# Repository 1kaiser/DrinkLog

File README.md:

# 💧 DrinkLog — Concept Universal Waterproof BLE Smart Bottle-Cap Hydration Tracker

<p align="center">

</p>

> [!NOTE]
> **Concept & Reference Design:** DrinkLog is currently a **pre-prototype hardware and software concept**. No physical PCB, enclosure, strain-gauge flexure, or live BLE/USB-C unit has been fabricated or bench-tested yet. All power budgets, mechanical tolerances, PCBWay deliverables, firmware modules, and companion code are validated in software/simulation only (`C++17` unit tests, `pytest`, programmatic DRC/STL/DXF checks, and Dawn WebGPU/WASM + Three.js renders). Review KiCad footprints, RF antenna clearance, IP67 seal compression, and mechanical fits before ordering prototype hardware.

**DrinkLog** is a conceptual, ultra-thin (`11.0 mm` added cap height), rechargeable, **IP67 waterproof USB-C** smart bottle-cap gripper proportioned at **`1.10 × D_cap`** (`33.6 mm` for standard PET water bottles up to `69.3 mm` for wide-mouth flasks) around a **universal `Ø 28.0 mm` drop-in PCBWay core** designed to measure fluid consumed from **pick-up / put-down gravimetric weight differences** and log every sip into **Android Health Connect** (`HydrationRecord`).

Everything needed to review, simulate, and prototype the concept — **3D-printable STLs**, **laser-cut flexure DXF**, **PCBWay Gerber/BOM/CPL & KiCad 8 files**, **firmware**, **Node.js + Clang `wasm32` + Native Dawn WebGPU animation (`webgpu-dawn-wasm/`)**, **interactive Three.js viewer (`web-threejs/`)**, and **BLE/Health Connect companion code** — lives in this repository.

---

## ✨ Key Highlights

* 📐 **`1.10 × D_cap` Zero-Overhang Proportions:** Instead of a bulky universal puck overhanging a small PET bottle, DrinkLog scales cleanly across 4 standard cap tiers (`33.6 / 45.1 / 52.8 / 69.3 mm`) while sharing **one universal `Ø 28.0 mm` PCBWay PCBA + `Ø 30.0 mm` 301-SS flexure core** across all 4 shells:
  | Tier Preset | Bottle Type | Nominal Cap OD (`D_cap`) | DrinkLog OD (`1.10 × D_cap`) | Battery |
  | :--- | :--- | :---: | :---: | :---: |
  | **`pet_30`** *(Default)* | Standard PET Water / Soda (`28 mm` neck) | `30.5 mm` | **`33.6 mm`** | `401520` (`100 mAh`, ~`8.0 mo`) |
  | **`sport_40`** | Sports / Wide PET (`38 mm` neck) | `41.0 mm` | **`45.1 mm`** | `302030` (`150 mAh`, ~`11.8 mo`) |
  | **`flask_48`** | Insulated Standard Flask | `48.0 mm` | **`52.8 mm`** | `302030` (`150 mAh`, ~`11.8 mo`) |
  | **`wide_63`** | Wide-Mouth Hydro Flask / Nalgene | `63.0 mm` | **`69.3 mm`** | `302030` (`150 mAh`, ~`11.8 mo`) |
* ⚖️ **Moment-Cancelling 3-Spoke Flexure:** Universal **`Ø 30.0 mm × 0.8 mm`** laser-cut `301-SS` flexure with `4× BF1000-2AA` (`1000 Ω`) full Wheatstone bridge and `0.35 mm` drop hard-stops rejects off-axis tilt moments and twisting torque.
* 🔋 **8–12 Months per Charge (`6.4 µA` Standby):** `NAU7802YG` (`QFN-16`) switches its internal `2.4 V AVDD` LDO to **High-Z** between lifts (`0 µA` bridge leak), paired with a `0.9 µA` **Bosch BMA400** wake-on-lift IMU.
* 🔌 **Waterproof USB-C Charging + Dual Debug:** Uses an **Amphenol `12402448E512A` IPX8 mid-mount USB-C** port + captive `TPU 85A` plug + **Raytac `MDBT50Q-1MV2` (`nRF52840`)** for native USB 2.0 CDC serial calibration (`s`, `t`, `c <g>`, `d`, `b` UF2/DFU) AND a zero-height bottom **Tag-Connect `TC2030` SWD** footprint.
* 🏭 **Turnkey PCBWay Ready:** Full KiCad 8 project (`Ø 28.0 mm`, `0.8 mm` 4L ENIG), RS-274X Gerbers + Excellon drills, matching 1:1 BOM & Centroid CPL CSVs, `Ø 30.0 mm` sheet-metal DXF, and 8 split 3D-printable STLs.

---

## 🧩 Hardware Components & Architecture

<details>
<summary><b>🔬 1. Physics & Gravimetric Sensing Mechanics (Why Cap-Lift Works)</b></summary>

1. **Cap-Lift Load Path (`100%` Bottle Mass):** When a bottle rests on a desk, its cap carries zero load. DrinkLog embeds a **flush-folding finger bail** on the upper housing; lifting the bottle by the bail routes `100%` of gravity through the `0.8 mm` flexure between the upper puck and lower cap clamp.
2. **Pre-Drink vs. Post-Drink Delta:** Because screw caps are removed while drinking, each stabilized lift records $m_k$:
   $$\Delta V_{\text{mL}} = \frac{m_{k-1} - m_k}{\rho_{\text{water}}}, \qquad \rho_{\text{water}} \approx 1.00\text{ g/mL}$$
   * **$\Delta m \ge +15\text{ g}$:** Logged as **fluid consumed** (`delta_ml > 0`).
   * **$\Delta m \le -25\text{ g}$:** Classified as a **bottle refill** (`delta_ml = 0`, baseline updated).
   * **`|m| < 45 g` (Unscrew Auto-Tare):** When the cap is unscrewed, firmware gently tracks zero offset (`0.8 * old + 0.2 * median`), eliminating thermal drift.
3. **Inertial & Tilt Compensation:** When `BMA400` detects a steady vertical hold (`a_z ∈ [0.85g, 1.15g]`, tilt `< 15°`), upward hand acceleration is removed via $m = F_z / a_z$.

</details>

<details>
<summary><b>🛒 2. Emoji-Tagged Component Matrix & Multi-Variant BOM (<code>docs/BOM.csv</code>)</b></summary>

| Emoji | Subsystem | Primary Component (V2 PCBWay / V1) | Key Specs & Role | Links |
| :---: | :--- | :--- | :--- | :--- |
| 🧠 | **MCU + BLE** | **Raytac `MDBT50Q-1MV2`** (`nRF52840`) *(V1: Seeed XIAO nRF52840 / ESP32-C6)* | Native USB 2.0 `D+/D-` + SWD + BLE 5.0 (`~5 µA` idle; chosen over `nRF54L15` which lacks native USB PHY) | [`BOM.csv`](docs/BOM.csv) |
| 🔌 | **Waterproof USB-C** | **Amphenol `12402448E512A`** + `USBLC6-2SC6` + `2× 5.1kΩ` | IPX8 mid-mount O-ring USB-C, ESD/TVS protection, CC1/CC2 5V negotiation | [`PCBWAY_ORDER_GUIDE.md`](hardware/pcbway/PCBWAY_ORDER_GUIDE.md) |
| 🔋 | **Charger & LDO** | **TI `BQ25180YBGR`** + **`TPS7A0233PDBVR`** + **`302030` 150 mAh LiPo** | `15 nA` ship mode, I²C programmable `VBATREG`, `25 nA` 3.3V LDO, `3.0 mm` pouch | [`DESIGN_SPEC.md`](docs/DESIGN_SPEC.md) |
| 📡 | **Wake IMU** | **Bosch `BMA400`** (`I2C 0x14`) | `0.9 µA` at `25 Hz` auto-wake interrupt (`INT1 -> D1`); validates vertical hold | [`sensor_drivers.h`](firmware/include/sensor_drivers.h) |
| ⚖️ | **24-bit Bridge ADC** | **Nuvoton `NAU7802YG`** (`QFN-16`, `I2C 0x2A`) | Internal `2.4 V AVDD` LDO goes **High-Z** in sleep (`0 µA` bridge leak) | [`circuit_pinout_v1.md`](hardware/netlist/circuit_pinout_v1.md) |
| 📏 | **Strain / Load Cell** | **`4× BF1000-3AA` (`1000 Ω`)** on `0.8 mm` `301-SS` flexure *(Alt: TE `FX29` I²C)* | `2.4 mA` active bridge draw (`3×` lower than `350 Ω` cells); `0.35 mm` hard-stop | [`09_flexure_3spoke_0p8mm_301SS.dxf`](cad/stl_print_parts/09_flexure_3spoke_0p8mm_301SS.dxf) |
| 🐛 | **Debug Header** | **Tag-Connect `TC2030-IDC-NL`** (Bottom Pads) + `SW1` DFU button | Zero added thickness 6-pin SWD + UART pogo interface | [`DrinkLog_V2.kicad_pcb`](hardware/pcbway/kicad/DrinkLog_V2.kicad_pcb) |

*Note: **Adafruit SHT4x Trinkey (`ATSAMD21E18`)** has no BLE/battery support and **RP2040/Pico W** leaks `~500–1500 µA` in sleep (~4–10 days battery); see [`docs/DESIGN_SPEC.md`](docs/DESIGN_SPEC.md) for the full 7-board power benchmark.*

</details>

<details>
<summary><b>🌊 3. Waterproof IP67 USB-C Charging & Dual Debug Architecture</b></summary>

* **2-Layer Waterproofing:**
  1. **Connector Seal:** `Amphenol 12402448E512A` mid-mount IPX8 USB-C receptacle seals directly against the enclosure perimeter lip, backed by a captive **`TPU 85A` port plug** (`08_usbc_waterproof_plug_tpu.stl`) to block soap/grit during bottle washing.
  2. **Housing Seal:** Top lid compresses a **`Ø 58 × 1.5 mm` silicone O-ring** into the upper puck gland; flexure leads pass through a `4.0 mm` **neutral-cure silicone RTV** gland in the hub plate.
* **USB-C Live Debug & Calibration CLI (`0 µA` Unplugged Penalty):**
  Plug into any PC with a standard USB-C cable (`115200` baud) while `ENABLE_USB_DEBUG_CLI=1` in [`main_nrf52.cpp`](firmware/src/main_nrf52.cpp):
  * `s` → JSON telemetry (`uptime_s`, `vbat_mv`, `last_g`, `zero`, `cpg`, `pending`)
  * `t` → Tare unweighted cap offset
  * `c 500` → Two-point calibration with a known `500 g` weight
  * `d` → Dump queued offline hydration events
  * `b` → Reboot directly into **UF2/DFU USB-C bootloader**
* **Hardware SWD Recovery:** Bottom-side **Tag-Connect `TC2030-IDC-NL`** pads expose `VDD_3V3`, `SWDIO`, `nRESET`, `SWDCLK`, `GND`, `UART_TX` without adding vertical height.

</details>

---

## 🏭 PCBWay Fabrication, PCBA & 3D Printing Package

<details>
<summary><b>📦 4. Ready-to-Upload PCBWay Order Files (Gerbers, KiCad 8, BOM, CPL, Laser DXF)</b></summary>

| Service | File(s) to Upload | Key Order Settings |
| :--- | :--- | :--- |
| **PCB Fabrication** | [`hardware/pcbway/fab/DrinkLog_V2_PCBWay_Gerbers.zip`](hardware/pcbway/fab/DrinkLog_V2_PCBWay_Gerbers.zip) | `4 Layers`, `Ø 28.0 mm`, **`0.8 mm` thick**, **ENIG-RoHS** |
| **Turnkey PCBA** | [`DrinkLog_V2_PCBWay_BOM.csv`](hardware/pcbway/pcba/DrinkLog_V2_PCBWay_BOM.csv) + [`DrinkLog_V2_PCBWay_CPL_PickAndPlace.csv`](hardware/pcbway/pcba/DrinkLog_V2_PCBWay_CPL_PickAndPlace.csv) | **Top-side SMT only** (`17` SMT parts; `J2/J3/J4` marked `PCB_PAD_DNP`) |
| **KiCad 8 Source** | [`hardware/pcbway/kicad/`](hardware/pcbway/kicad/) (`DrinkLog_V2.kicad_pro/.kicad_sch/.kicad_pcb`) | Generated & verified via [`generate_pcbway_package.py`](hardware/pcbway/generate_pcbway_package.py) |
| **Sheet Metal Laser** | [`cad/stl_print_parts/09_flexure_3spoke_0p8mm_301SS.dxf`](cad/stl_print_parts/09_flexure_3spoke_0p8mm_301SS.dxf) | **`0.8 mm` 301 Stainless Steel (Full Hard)**, laser cut |

Full step-by-step instructions: [`hardware/pcbway/PCBWAY_ORDER_GUIDE.md`](hardware/pcbway/PCBWAY_ORDER_GUIDE.md).

</details>

<details>
<summary><b>🖨️ 5. Split 3D-Printable STL Parts (<code>cad/stl_print_parts/</code> &amp; <code>universal_cap_gripper.scad</code>)</b></summary>

| STL / CAD File | Qty | Material | Description |
| :--- | :---: | :--- | :--- |
| [`01_scroll_collar_knurled_u65.stl`](cad/stl_print_parts/01_scroll_collar_knurled_u65.stl) | 1 | PA12 / PETG | Outer knurled scroll ring (`26–65 mm` cap OD) |
| [`02_chuck_hub_plate_u65.stl`](cad/stl_print_parts/02_chuck_hub_plate_u65.stl) | 1 | PA12 / PETG | Concentric 3-jaw carrier w/ `4 mm` RTV wire gland |
| [`03_gripper_jaw_x3.stl`](cad/stl_print_parts/03_gripper_jaw_x3.stl) | **3** | PA12 / PETG | Sliding clamp jaws |
| [`04_jaw_grip_pad_tpu_x3.stl`](cad/stl_print_parts/04_jaw_grip_pad_tpu_x3.stl) | **3** | **TPU 85A** | High-friction bottle-cap grip pads |
| [`05_upper_puck_housing_usbc_ip67.stl`](cad/stl_print_parts/05_upper_puck_housing_usbc_ip67.stl) | 1 | PA12 / PETG | Houses `Ø 28 mm` PCB, `401520 / 302030` LiPo, IPX8 USB-C bezel & O-ring groove |
| [`06_top_waterproof_lid.stl`](cad/stl_print_parts/06_top_waterproof_lid.stl) | 1 | PA12 / PETG | O-ring compression lid + 4× M2 countersunk screws |
| [`07_folding_finger_bail.stl`](cad/stl_print_parts/07_folding_finger_bail.stl) | 1 | PA12 / CF-PETG | Flush-folding bottle-lift bail |
| [`08_usbc_waterproof_plug_tpu.stl`](cad/stl_print_parts/08_usbc_waterproof_plug_tpu.stl) | 1 | **TPU 85A** | Secondary captive IP67 USB-C washdown plug |
| [`universal_cap_gripper.scad`](cad/universal_cap_gripper.scad) | — | OpenSCAD | Parametric source (`universal_65` / `compact_45`, `flexure_3spoke` / `fx29_yoke`) |

Full 3D assemblies are also exported as color-coded `.glb` / `.stl` in [`cad/outputs/`](cad/outputs/).

</details>

---

## 💻 Firmware, Power Model & Google Health Connect App

<details>
<summary><b>⚡ 6. Firmware Targets, BLE GATT Binary Protocol &amp; Pipeline</b></summary>

* **Pipeline Flowchart:** [`hardware/diagrams/firmware_ble_pipeline.png`](hardware/diagrams/firmware_ble_pipeline.png) (Draw.io XML audited to `0` overlaps)
* **PlatformIO Environments ([`firmware/platformio.ini`](firmware/platformio.ini)):**
  * `xiao_nrf52840_bma400` *(Primary V1 / V2 `MDBT50Q`: `6.4 µA` sleep → **~11.8 months** on `150 mAh` LiPo)*
  * `xiao_nrf52840_sense` *(Onboard `LSM6DS3TR-C` w/ gyro OFF `CTRL2_G=0x00` → **~3.2 months**)*
  * `xiao_esp32c6_bma400` *(Budget `~$6` MCU w/ `RTC_DATA_ATTR` state retention & Wi-Fi off → **~5.4 months**)*
* **BLE GATT Service (`7a4b0001-3c9e-4f1a-9b2d-8e5c10293847`) + Battery Service `0x180F`:**
  * `0002` **Event Notify/Read (`12 B`, `<IIhH`):** `uint32 seq`, `uint32 uptime_s`, `int16 delta_ml`, `uint16 bottle_mass_g`
  * `0003` **ACK Write (`4 B`, `<I`):** `uint32 last_acked_seq` (clears 64-event non-volatile ring buffer)
  * `0004` **Status Read (`8 B`, `<IHH`):** `uint32 device_uptime_s`, `uint16 vbat_mv`, `uint16 last_mass_g`

</details>

<details>
<summary><b>📱 7. Android Health Connect (<code>HydrationRecord</code>) &amp; Python BLE Bridge</b></summary>

Because legacy Google Fit APIs reach end-of-service in late 2026, [`companion/android-health-connect/`](companion/android-health-connect/) writes directly to on-device **Android Health Connect**:
* [`BleGattProtocol.kt`](companion/android-health-connect/src/main/java/com/drinklog/app/BleGattProtocol.kt) — Little-endian packet codec & offline timestamp reconstruction (`sipEnd = now - (deviceUptimeS - ev.uptimeS)`).
* [`HealthConnectSyncManager.kt`](companion/android-health-connect/src/main/java/com/drinklog/app/HealthConnectSyncManager.kt) — Inserts `HydrationRecord(volume = Volume.milliliters(...))` with idempotent `clientRecordId = "drinklog-$mac-$seq"`.
* [`DrinkLogBleClient.kt`](companion/android-health-connect/src/main/java/com/drinklog/app/DrinkLogBleClient.kt) — Writes BLE ACK (`0003`) **only after** Health Connect confirms persistence.
* [`companion/python-ble-bridge/cap_ble_receiver.py`](companion/python-ble-bridge/cap_ble_receiver.py) — Desktop `bleak` receiver + `--simulate` binary loopback test.

</details>

---

## 🧪 Verification & Quickstart Commands

```bash
# 1. Native C++17 Firmware DSP, Auto-Tare, Inertial & Ring-Buffer Unit Tests
g++ -std=c++17 -Wall -Wextra -Werror -Ifirmware/include \
  firmware/tests/test_hydration_core.cpp -o /tmp/test_hydration_core && /tmp/test_hydration_core

# 2. Render 3D Animation via Node.js + Clang wasm32 + Native Dawn WebGPU (Zero Browser)
cd webgpu-dawn-wasm && npm run build:wasm && npm run build:hud && npm run render && cd ..
# Keyframe sheet saved to outputs/drinklog_dawn_webgpu_keyframes.png

# 3. OR Launch Interactive Three.js WebGL Browser Viewer
node web-threejs/serve.mjs --port 8080

# 3. Generate PCBWay Gerbers, KiCad 8 Files, BOM/CPL, CAD STLs/DXF & Diagrams
python hardware/pcbway/generate_pcbway_package.py
python hardware/diagrams/generate_diagrams.py
python cad/generate_cad_assets.py
python cad/export_print_parts.py

# 4. Run Python Protocol, Power Model & Manufacturing Package Integrity Tests
python companion/python-ble-bridge/power_budget_model.py
python companion/python-ble-bridge/cap_ble_receiver.py --simulate
pytest -v companion/python-ble-bridge/tests/
```

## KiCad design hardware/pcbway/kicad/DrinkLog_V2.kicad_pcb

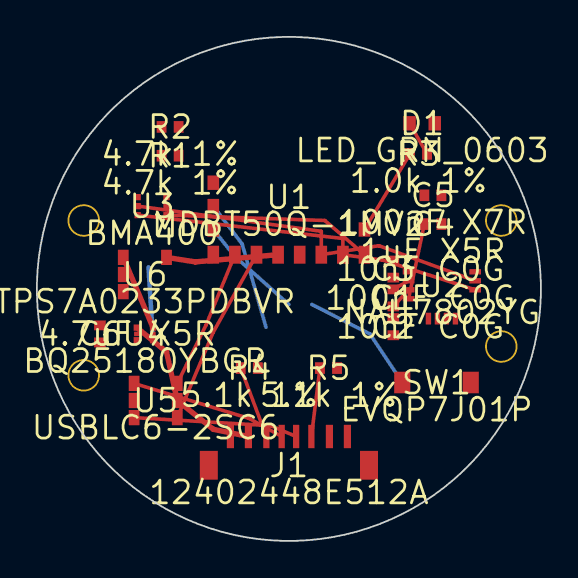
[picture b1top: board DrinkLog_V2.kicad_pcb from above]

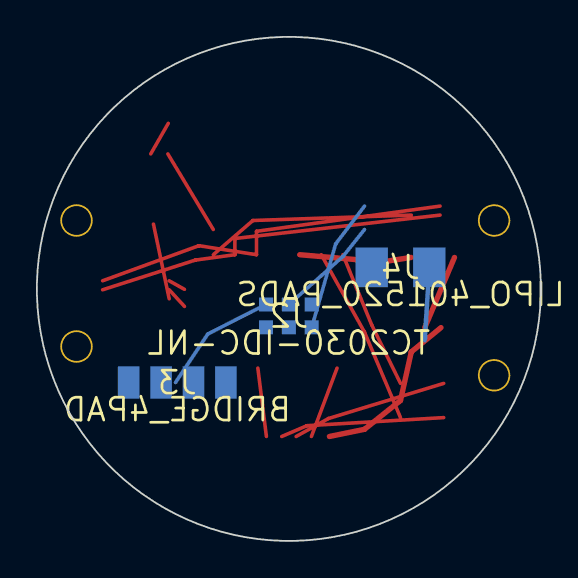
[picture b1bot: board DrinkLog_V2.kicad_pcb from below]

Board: 4 copper layers, 28.0 x 28.0 mm, 23 parts (3 on the bottom side), 22 nets.

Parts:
C1: 100nF C0G; 0402
C2, C3: 10nF C0G; 0402
C4: 1uF X5R; 0402
C5: 100nF X7R; 0402
C6: 4.7uF X5R; 0402
D1: LED_GRN_0603; 0603
J1: 12402448E512A; USB_C_MidMount_IPX8
J2: TC2030-IDC-NL; TC2030_6PAD
J3: BRIDGE_4PAD; PAD_4x1.8mm
J4: LIPO_401520_PADS; PAD_2x2.2mm
R1, R2: 4.7k 1%; 0402
R3: 1.0k 1%; 0402
R4, R5: 5.1k 1%; 0402
SW1: EVQP7J01P; 3.5x2.9mm
U1: MDBT50Q-1MV2; MDBT50Q_15.0x10.5
U2: NAU7802YG; QFN-16_4x4mm
U3: BMA400; LGA-12_2x2
U4: BQ25180YBGR; DSBGA-8_1.6x1.1
U5: USBLC6-2SC6; SOT-23-6
U6: TPS7A0233PDBVR; SOT-23-5

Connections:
AGND: C2.2, C3.2, C4.2, C5.2, J3.2, U2.6
AVDD: C4.1, J3.1, U2.4
GND: C6.2, D1.2, J1.A1, J1.B12, J1.SH1, J1.SH2, J2.5, J4.2, R4.2, R5.2, SW1.2, U1.GND, U3.GND, U3.SDO, U4.GND, U5.2, U6.GND
I2C_SCL: R2.2, U1.SCL, U2.14, U3.SCL, U4.SCL
I2C_SDA: R1.2, U1.SDA, U2.15, U3.SDA, U4.SDA
IMU_INT1: U1.INT1, U3.INT1
LED_A: D1.1, R3.2
LED_STAT: R3.1, U1.LED
SWDCLK: J2.4, U1.SWDCLK
SWDIO: J2.2, U1.SWDIO
USB_CC1: J1.A5, R4.1
USB_CC2: J1.B5, R5.1
USB_DM: J1.A7, U1.DM, U5.3, U5.4
USB_DP: J1.A6, U1.DP, U5.1, U5.6
VBAT: J4.1, U4.BAT
VBG: C5.1, U2.5
VBUS_5V: J1.A4, J1.B4, U1.VBUS, U4.IN, U5.5
VDD_3V3: J2.1, R1.1, R2.1, U1.VDD, U3.VDD, U6.OUT
VIN1N: C1.2, C3.1, J3.4, U2.2
VIN1P: C1.1, C2.1, J3.3, U2.3
VSYS: C6.1, U4.SYS, U6.EN, U6.IN
nRESET: J2.3, SW1.1, U1.nRST

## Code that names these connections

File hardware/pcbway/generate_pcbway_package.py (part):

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    parts.append(PartDef(
        "R4", "5.1k 1%", "Yageo", "RC0402FR-075K1L",
        "USB-C CC1 5.1 kOhm 1% Pull-Down Resistor", "0402", "SMT", "LCSC: C25905",
        -2.2, -4.4, 0.0, "Top", 1.2, 0.7, _rect_pads_2pin(0.95, 0.55, 0.65, "USB_CC1", "GND")
    ))
    parts.append(PartDef(
        "R5", "5.1k 1%", "Yageo", "RC0402FR-075K1L",
        "USB-C CC2 5.1 kOhm 1% Pull-Down Resistor", "0402", "SMT", "LCSC: C25905",
        2.2, -4.4, 0.0, "Top", 1.2, 0.7, _rect_pads_2pin(0.95, 0.55, 0.65, "USB_CC2", "GND")
    ))

    # U4: TI BQ25180YBGR Li-Ion Charger (-8.0, -2.5)
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    # Compact 0402 Passives, 0603 LED, and Reset Switch — all verified inside Ø28.0 mm
    parts.extend([
        PartDef("C1", "100nF C0G", "Murata", "GRM1555C1H104FA01", "Differential Bridge Filter Cap", "0402", "SMT", "LCSC: C1525",
                5.8, -0.5, 90.0, "Top", 1.2, 0.7, _rect_pads_2pin(0.95, 0.55, 0.65, "VIN1P", "VIN1N")),
        PartDef("C2", "10nF C0G", "Murata", "GRM1555C1H103JA01", "VIN1P Common-Mode Cap", "0402", "SMT", "LCSC: C15195",
                5.8, -2.1, 90.0, "Top", 1.2, 0.7, _rect_pads_2pin(0.95, 0.55, 0.65, "VIN1P", "AGND")),
        PartDef("C3", "10nF C0G", "Murata", "GRM1555C1H103JA01", "VIN1N Common-Mode Cap", "0402", "SMT", "LCSC: C15195",
                5.8, 1.1, 90.0, "Top", 1.2, 0.7, _rect_pads_2pin(0.95, 0.55, 0.65, "VIN1N", "AGND")),
        PartDef("C4", "1uF X5R", "Samsung", "CL05A105KA5NQNC", "NAU7802 AVDD Decoupling Cap", "0402", "SMT", "LCSC: C52923",
                8.0, 3.6, 0.0, "Top", 1.2, 0.7, _rect_pads_2pin(0.95, 0.55, 0.65, "AVDD", "AGND")),
        PartDef("C5", "100nF X7R", "Samsung", "CL05B104KO5NNNC", "NAU7802 VBG & MCU Decoupling", "0402", "SMT", "LCSC: C1525",
                8.0, 5.2, 0.0, "Top", 1.2, 0.7, _rect_pads_2pin(0.95, 0.55, 0.65, "VBG", "AGND")),
        PartDef("C6", "4.7uF X5R", "Samsung", "CL05A475MP5NRNC", "BQ25180 VSYS & VBAT Bulk Cap", "0402", "SMT", "LCSC: C23733",
                -10.5, -2.5, 90.0, "Top", 1.2, 0.7, _rect_pads_2pin(0.95, 0.55, 0.65, "VSYS", "GND")),
        PartDef("R1", "4.7k 1%", "Yageo", "RC0402FR-074K7L", "I2C SDA Pull-Up Resistor", "0402", "SMT", "LCSC: C25900",
                -6.6, 7.4, 0.0, "Top", 1.2, 0.7, _rect_pads_2pin(0.95, 0.55, 0.65, "VDD_3V3", "I2C_SDA")),
        PartDef("R2", "4.7k 1%", "Yageo", "RC0402FR-074K7L", "I2C SCL Pull-Up Resistor", "0402", "SMT", "LCSC: C25900",
                -6.6, 9.0, 0.0, "Top", 1.2, 0.7, _rect_pads_2pin(0.95, 0.55, 0.65, "VDD_3V3", "I2C_SCL")),
        PartDef("R3", "1.0k 1%", "Yageo", "RC0402FR-071KL", "Status LED Current Limit", "0402", "SMT", "LCSC: C11702",
                7.2, 7.5, 0.0, "Top", 1.2, 0.7, _rect_pads_2pin(0.95, 0.55, 0.65, "LED_STAT", "LED_A")),
        PartDef("D1", "LED_GRN_0603", "Kingbright", "APT1608ZGC", "0603 Green Lock Status LED", "0603", "SMT", "LCSC: C72043",
                7.4, 9.2, 0.0, "Top", 1.6, 0.8, _rect_pads_2pin(1.4, 0.7, 0.8, "LED_A", "GND")),
        PartDef("SW1", "EVQP7J01P", "Panasonic", "EVQP7J01P", "Recessed Tactile Reset / DFU Button", "3.5x2.9mm", "SMT", "DigiKey: P16758CT-ND",
                8.2, -5.2, 0.0, "Top", 3.5, 2.9, _rect_pads_2pin(3.8, 0.9, 1.2, "nRESET", "GND")),
    ])

    # Bottom-side Pads (Zero added height)
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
